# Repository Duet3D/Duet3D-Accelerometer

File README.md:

# Duet3D-Accelerometer
A standalone accelerometer board using the LIS3DH MEMS digital motion sensor. It is designed to plug into the SPI daughterboard header on Duet 2 and 3 mainboards.

Product Page:
[https://www.duet3d.com/duet3d-accelerometer](https://www.duet3d.com/duet3d-accelerometer)

Documentation is here:

[Duet 3 Accelerometer Documentation](https://docs.duet3d.com/en/Duet3D_hardware/Accessories/Duet3D_Accelerometer)

licensed under the "CERN-OHL-S v2" or any later version plus the "Additional Duet3D Licence Terms",
see https://github.com/Duet3D/Duet3-Mainboard-6HC/blob/master/LICENSE

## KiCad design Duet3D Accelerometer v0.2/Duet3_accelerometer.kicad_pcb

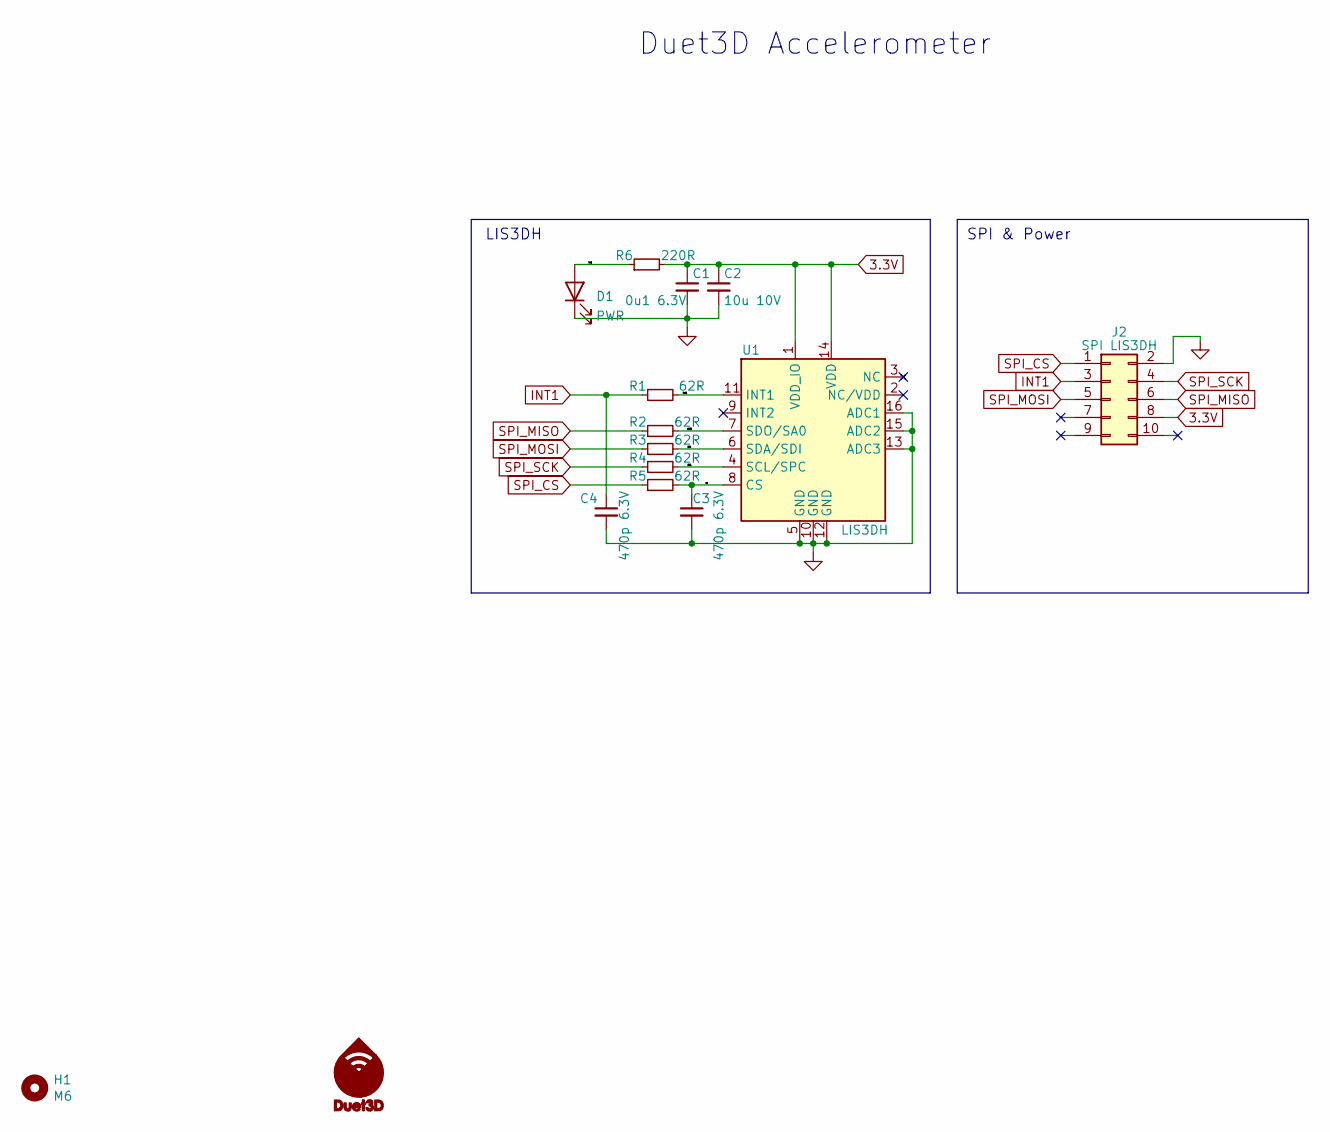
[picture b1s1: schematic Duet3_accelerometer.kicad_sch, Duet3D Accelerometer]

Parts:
C1: 0u1 6.3V; C_0402_1005Metric_Wbry; Part Number 1uF 6.3V X7R 0402
C2: 10u 10V; C_0603_1608Metric_Wbry; Part Number 10u 10V 10% X7R
C3, C4: 470p 6.3V; C_0402_1005Metric_Wbry; Part Number 6.3V 10% X7R 0401
D1: PWR; LED_0603_1608Metric; Part Number 150060VS75000 or equivalent Green
H1: M6; MountingHole_6mm
J2: SPI LIS3DH; IDC-Header_2x05_P2.54mm_Vertical
M1: Logo_Duet3d_New; LOGO_NEW_Duet3D_vertical_6mm_no_mask
R1, R2, R3, R4, R5: 62R; R_0402_1005Metric_Wbry; Part Number 62R 1% 0402
R6: 220R; R_0402_1005Metric_Wbry; Part Number 62R 1% 0402
U1: LIS3DH; LGA-16_3x3mm_P0.5mm_LISD3H; Part Number LIS3DHTR

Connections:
3.3V: C1.1, C2.1, J2.8, R6.2, U1.1 (VDD_IO), U1.14 (VDD)
/SCL: R4.2, U1.4 (SCL/SPC)
/SDI: R3.2, U1.6 (SDA/SDI)
/SDO: R2.2, U1.7 (SDO/SA0)
/cs: C3.1, R5.2, U1.8 (CS)
/int1: R1.2, U1.11 (INT1)
/led: D1.2 (A), R6.1
GND: C1.2, C2.2, C3.2, C4.2, D1.1 (K), J2.2, U1.5 (GND), U1.10 (GND), U1.12 (GND), U1.13 (ADC3), U1.15 (ADC2), U1.16 (ADC1)
INT1: C4.1, J2.3, R1.1
SPI_CS: J2.1, R5.1
SPI_MISO: J2.6, R2.1
SPI_MOSI: J2.5, R3.1
SPI_SCK: J2.4, R4.1

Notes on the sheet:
Duet3D Accelerometer
LIS3DH
SPI & Power

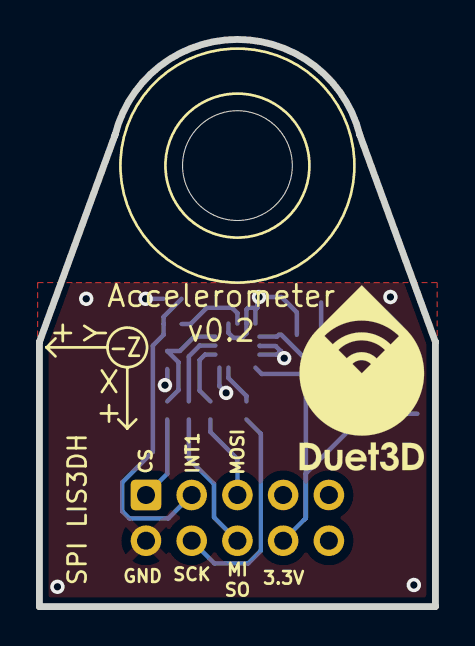
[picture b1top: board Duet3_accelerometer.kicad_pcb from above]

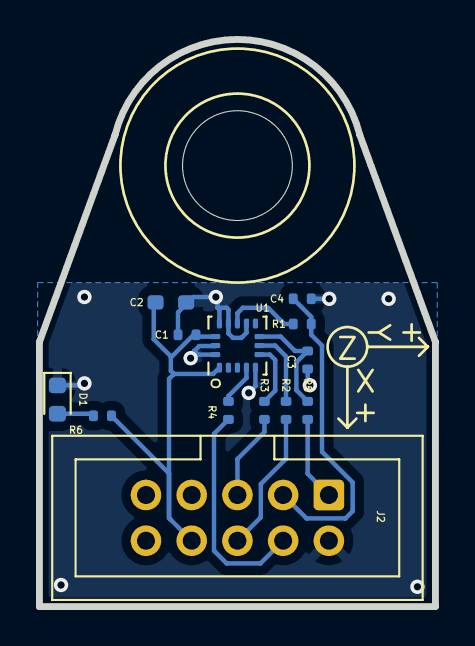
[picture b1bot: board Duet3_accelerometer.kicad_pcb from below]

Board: 2 copper layers, 22.0 x 31.5 mm, 15 parts (13 on the bottom side), 13 nets.

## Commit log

2023-07-21 Added v0.2 source
2023-08-15 Added STEP file
